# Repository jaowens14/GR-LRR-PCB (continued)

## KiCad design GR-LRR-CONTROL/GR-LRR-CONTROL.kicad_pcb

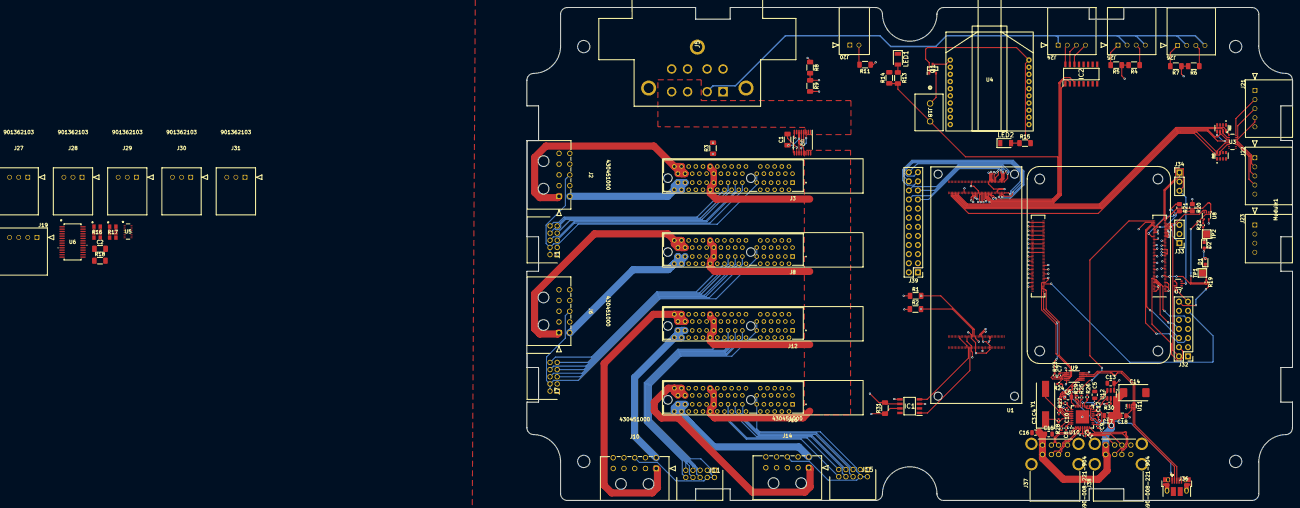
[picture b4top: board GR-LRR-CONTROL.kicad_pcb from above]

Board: 4 copper layers, 213.7 x 137.6 mm, 106 parts (0 on the bottom side), 190 nets.

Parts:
C1: 0.1uF; C_1206_3216Metric_Pad1.33x1.80mm_HandSolder
C2: 10uF; C_1206_3216Metric_Pad1.33x1.80mm_HandSolder
C3, C4: 27pF; C_0402_1005Metric
C5, C6, C13, C15, C16, C17, C18: 10u; C_0805_2012Metric
C7, C8, C9, C10, C11, C12: 100n; C_0402_1005Metric
C14: 100uF; CP_EIA-7343-31_Kemet-D
D1: LED Green; LED_0603_1608Metric
D2: LED Red; LED_0603_1608Metric
IC1: TJA1049T,118
IC2: MC1413DR2G; SOIC127P600X175-16N
J1, J7, J11, J15: 87833-1019
J2, J6, J10, J14: 430451000
J3, J8, J12, J16: 10018783-10101TLF; AMPHENOL_10018783-10101TLF
J5: DT13-08PB; DT1308PB
J18: 691137710002
J19, J23: 901362104
J20: 901362102
J21: ENC1; 901362105
J22: ENC2; 901362105
J24: LED; 901362104
J25: UT1; 901362104
J26: UT2; 901362104
J27, J28, J29, J30, J31: 901362103
J32: Conn_02x07_Odd_Even; PinHeader_2x07_P2.54mm_Vertical
J33, J34: Conn_01x03; PinHeader_1x03_P2.54mm_Vertical
J36: USB_OTG; USB_Micro-B_EDAC_UCON00686
J37, J38: 690-008-221-904; MOLEX_USB_67298-4090
J39: Conn_02x12_Counter_Clockwise; PinHeader_2x12_P2.54mm_Vertical
LED1, LED2: QTLP650C2TR; LEDC3216X130N
Module1: ComputeModule4; Raspberry-Pi-4-Compute-Module
Q1: BSS806NH6327XTSA1; SOT95P240X110-3N
R1, R2, R18: 10k; R_1206_3216Metric_Pad1.30x1.75mm_HandSolder
R3, R31: 120; R_1206_3216Metric_Pad1.30x1.75mm_HandSolder
R4, R6: 4k; R_1206_3216Metric_Pad1.30x1.75mm_HandSolder
R5, R7: 1k 1/8w; R_1206_3216Metric_Pad1.30x1.75mm_HandSolder
R8: 100k 1/8W; R_1206_3216Metric_Pad1.30x1.75mm_HandSolder
R9: 10k 1/8w; R_1206_3216Metric_Pad1.30x1.75mm_HandSolder
R10, R12: YC164-JR-072KL; RESCAXE80P320X160X70-8N
R11, R14: 10k 1/8W; R_1206_3216Metric_Pad1.30x1.75mm_HandSolder
R13, R15: 86ohm, 1/10w; R_1206_3216Metric_Pad1.30x1.75mm_HandSolder
R16, R17: CAY16-221J4LF; CAY16_221J4LF
R19, R22: 1k; R_0402_1005Metric
R20: 0R; R_0805_2012Metric_Pad1.20x1.40mm_HandSolder
R21: nf; R_0805_2012Metric_Pad1.20x1.40mm_HandSolder
R23, R24: 2.2K 1%; R_0402_1005Metric
R25, R26, R27, R29: 36K 1%; R_0402_1005Metric
R28: 12K 1%; R_0402_1005Metric
R30: 15K 1%; R_0402_1005Metric
TP1, TP2: TestPoint; TestPoint_Pad_2.0x2.0mm
U1: ABX00042; MODULE_ABX00042_2
U2: INA260AIPWR; PW0016A_N
U3: 1k; RES_YC248_4X1P6_YAG
U4: XB3-24AST-J
U5: YC248-JR-0710KL; RES_YC248_4X1P6_YAG
U6: PCA9685PW; SOT361-1_NXP
U7, U8: 74LVC1G07SE-7; SOT-353_SC-70-5
U9: FSUSB42MUX; MSOP-10_3x3mm_P0.5mm
U10: USB2514B-I/M2; QFN-36-1EP_6x6mm_P0.5mm_EP3.7x3.7mm
U11: TPD4EUSB30; USON-10_2.5x1.0mm_P0.5mm
U12: AP22653W6; SOT-23-6
Y1: 24MHz; Crystal_SMD_HC49-SD

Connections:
3.3V: C1.2, C5.1, C6.1, C7.1, C8.1, C9.1, C10.1, C11.1, C12.1, D1.2 (A), D2.2 (A), IC1.5 (SPLIT), J5.6, Module1.84 (+3.3v_(Output)), Module1.86 (+3.3v_(Output)), Q1.3 (D), R11.1, R20.1, U2.10 (VS), U4.1 (VCC), U8.5 (VCC), U9.1 (VCC), U10.5 (VDDA33), U10.10 (VDDA33), U10.15 (VDD33), U10.23 (VDD33), U10.27 (VBUS_DET), U10.29 (VDDA33), U10.36 (VDDA33)
5V: C2.1, C13.1, IC1.3 (VCC), J5.7, J19.1, J21.1, J22.1, J23.1, J27.2, J28.2, J29.2, J30.2, J31.2, Module1.77 (+5v_(Input)), Module1.79 (+5v_(Input)), Module1.81 (+5v_(Input)), Module1.83 (+5v_(Input)), Module1.85 (+5v_(Input)), Module1.87 (+5v_(Input)), R1.1, R2.1, U1.J1_21 (VIN), U1.J1_32 (VIN), U1.J1_41 (VIN), U1.J1_48 (VIN), U6.28 (VDD), U7.5 (VCC), U12.1 (IN)
18V: J3.A21, J3.A22, J3.B21, J3.B22, J8.A21, J8.A22, J8.B21, J8.B22, J12.A21, J12.A22, J12.B21, J12.B22, J16.A21, J16.A22, J16.B21, J16.B22, U2.14 (IN-), U2.15 (IN-), U2.16 (IN-)
18V_IN: J5.3, J5.4, U2.1 (IN+), U2.2 (IN+), U2.3 (IN+), U2.12 (VBUS)
24V: J5.2, J24.1, J25.2, J25.4, J26.2, J26.4
/CM4_GPIO ( Ethernet, GPIO, SDCARD)/+1.8v: Module1.88 (+1.8v_(Output)), Module1.90 (+1.8v_(Output)), R21.1
/CM4_GPIO ( Ethernet, GPIO, SDCARD)/AIN0: J32.5, Module1.96 (AnalogIP0)
/CM4_GPIO ( Ethernet, GPIO, SDCARD)/AIN1: J32.6, Module1.94 (AnalogIP1)
/CM4_GPIO ( Ethernet, GPIO, SDCARD)/BT_nDis: J33.3, Module1.91 (BT_nDisable)
/CM4_GPIO ( Ethernet, GPIO, SDCARD)/EEPROM_nWP: J32.4, Module1.20 (EEPROM_nWP)
/CM4_GPIO ( Ethernet, GPIO, SDCARD)/GLOBAL_EN: J32.14, J34.1, Module1.99 (Global_EN)
/CM4_GPIO ( Ethernet, GPIO, SDCARD)/GPIO_VREF: Module1.78 (GPIO_VREF(1.8v/3.3v_Input)), R20.2, R21.2
/CM4_GPIO ( Ethernet, GPIO, SDCARD)/RUN_PG: J34.3, Module1.92 (RUN_PG), U7.2
/CM4_GPIO ( Ethernet, GPIO, SDCARD)/SYNC_IN: J32.8, Module1.16 (Ethernet_SYNC_IN(1.8v))
/CM4_GPIO ( Ethernet, GPIO, SDCARD)/SYNC_OUT: J32.9, Module1.18 (Ethernet_SYNC_OUT(1.8v))
/CM4_GPIO ( Ethernet, GPIO, SDCARD)/TV_OUT: J32.11, Module1.111 (VDAC_COMP)
/CM4_GPIO ( Ethernet, GPIO, SDCARD)/WL_nDis: J33.1, Module1.89 (WL_nDisable)
/CM4_GPIO ( Ethernet, GPIO, SDCARD)/nPWR_LED: Module1.95 (nPI_LED_PWR), U8.2
/CM4_GPIO ( Ethernet, GPIO, SDCARD)/nRPIBOOT: J32.2, Module1.93 (nRPIBOOT)
/CM4_HighSpeed/USB2_N: Module1.103 (USB2_N), U9.4 (D_N)
/CM4_HighSpeed/USB2_P: Module1.105 (USB2_P), U9.3 (D_P)
/CM4_HighSpeed/USBOTG_ID: Module1.101 (USB_OTG_ID), R23.1, R24.2, U9.2 (SEL)
/USB2-HUB/HD1_N: J37.2 (D-`), U10.1 (USBDM_DN1/PRT_DIS_M1)
/USB2-HUB/HD1_P: J37.3 (D+`), U10.2 (USBDP_DN1/PRT_DIS_P1)
/USB2-HUB/HD2_N: J37.6 (D-), U10.3 (USBDM_DN2/PRT_DIS_M2)
/USB2-HUB/HD2_P: J37.7 (D+), U10.4 (USBDP_DN2/PRT_DIS_P2)
/USB2-HUB/HD3_N: J38.2 (D-`), U10.6 (USBDM_DN3/PRT_DIS_M3)
/USB2-HUB/HD3_P: J38.3 (D+`), U10.7 (USBDP_DN3/PRT_DIS_P3)
/USB2-HUB/HD4_N: J38.6 (D-), U10.8 (USBDM_DN4/PRT_DIS_M4)
/USB2-HUB/HD4_P: J38.7 (D+), U10.9 (USBDP_DN4/PRT_DIS_P4)
/USB2-HUB/PWR1: U10.12 (PRTPWR1/BC_EN1), U12.3 (EN)
/USB2-HUB/USBD_N: J36.2 (D-), U9.8 (HSD1_M), U11.4 (D2+), U11.7
/USB2-HUB/USBD_P: J36.3 (D+), U9.9 (HSD1_P), U11.5 (D2-), U11.6
/USB2-HUB/USBH_N: U9.6 (HSD0_M), U10.30 (USBDM_UP)
/USB2-HUB/USBH_P: U9.7 (HSD0_P), U10.31 (USBDP_UP)
/USB2-HUB/VBUS: C14.1, C15.1, C16.1, C17.1, C18.1, J37.1 (VBUS`), J37.5 (VBUS), J38.1 (VBUS`), J38.5 (VBUS), U12.6 (OUT)
/USB2-HUB/nOCS1: U10.13 (OCS_N1), U10.17 (OCS_N2), U10.19 (OCS_N3), U10.21 (OCS_N4), U12.4 (nFault)
/nEXTRST: Module1.100 (nEXTRST), U10.26 (RESET_N)
A3: J39.20, U1.J2_79 (ADC_A3)
A4: J39.21, U1.J2_74 (ADC_A4)
A5: J39.22, U1.J2_76 (ADC_A5)
A6: J39.23, U1.J2_78 (ADC_A6)
A7: J39.24, U1.J2_80 (ADC_A7)
BATT+: J5.5, R8.1
BAT_MON_73_A0: J39.17, R8.2, R9.1, U1.J2_73 (ADC_A0)
CLAMP_C: J20.2, R11.2
D0 ESTOP DETECT: J18.2, J39.10, R13.2, R14.1, U1.J2_62 (PWM_7)
D1: J39.11, U1.J2_60 (PWM_6)
D2: J39.12, U1.J2_67 (PWM_5)
D3: J39.13, U1.J2_65 (PWM_4)
D4: J39.14, U1.J2_63 (PWM_3)
D5 Clamp: J39.15, U1.J2_61 (PWM_2)
D6: J39.16, U1.J2_59 (PWM_1)
D7 CS: J39.9, U1.J2_36 (SPI1_CS)
D8 COPI: J39.6, U1.J2_42 (SPI1_MOSI)
D9 CK: J39.8, U1.J2_38 (SPI1_CK)
D10 CIPO: J39.7, U1.J2_40 (SPI1_MISO)
DVR_+5VOUT_1: J1.2, J1.4, J2.8, J3.A11, J3.B11
DVR_+5VOUT_2: J6.8, J7.2, J7.4, J8.A11, J8.B11
DVR_+5VOUT_3: J10.8, J11.2, J11.4, J12.A11, J12.B11
DVR_+5VOUT_4: J14.8, J15.2, J15.4, J16.A11, J16.B11
DVR_A-/SIN-/LH1_1: J1.5, J3.A13
DVR_A-/SIN-/LH1_2: J7.5, J8.A13
DVR_A-/SIN-/LH1_3: J11.5, J12.A13
DVR_A-/SIN-/LH1_4: J15.5, J16.A13
DVR_A/A+_1: J2.1, J3.B29, J3.B30, J3.B31, J3.B32
DVR_A/A+_2: J6.1, J8.B29, J8.B30, J8.B31, J8.B32
DVR_A/A+_3: J10.1, J12.B29, J12.B30, J12.B31, J12.B32
DVR_A/A+_4: J14.1, J16.B29, J16.B30, J16.B31, J16.B32
DVR_A/SIN+_1: J1.6, J3.A14
DVR_A/SIN+_2: J7.6, J8.A14
DVR_A/SIN+_3: J11.6, J12.A14
DVR_A/SIN+_4: J15.6, J16.A14
DVR_B-/COS-/LH2_1: J1.7, J3.A15
DVR_B-/COS-/LH2_2: J7.7, J8.A15
DVR_B-/COS-/LH2_3: J11.7, J12.A15
DVR_B-/COS-/LH2_4: J15.7, J16.A15
DVR_BR/B-_1: J2.7, J3.A25, J3.A26, J3.A27, J3.A28
DVR_BR/B-_2: J6.7, J8.A25, J8.A26, J8.A27, J8.A28
DVR_BR/B-_3: J10.7, J12.A25, J12.A26, J12.A27, J12.A28
DVR_BR/B-_4: J14.7, J16.A25, J16.A26, J16.A27, J16.A28
DVR_B/A-_1: J2.6, J3.A29, J3.A30, J3.A31, J3.A32
DVR_B/A-_2: J6.6, J8.A29, J8.A30, J8.A31, J8.A32
DVR_B/A-_3: J10.6, J12.A29, J12.A30, J12.A31, J12.A32
DVR_B/A-_4: J14.6, J16.A29, J16.A30, J16.A31, J16.A32
DVR_B/COS+_1: J1.8, J3.A16
DVR_B/COS+_2: J7.8, J8.A16
DVR_B/COS+_3: J11.8, J12.A16
DVR_B/COS+_4: J15.8, J16.A16
DVR_CAN_1_+: IC1.7 (CANH), J3.A19, J8.A19, J12.A19, J16.A19, R3.1, R31.1
DVR_CAN_1_-: IC1.6 (CANL), J3.B19, J8.B19, J12.B19, J16.B19, R3.2, R31.2
DVR_C/B+_1: J2.2, J3.B25, J3.B26, J3.B27, J3.B28
DVR_C/B+_2: J6.2, J8.B25, J8.B26, J8.B27, J8.B28
DVR_C/B+_3: J10.2, J12.B25, J12.B26, J12.B27, J12.B28
DVR_C/B+_4: J14.2, J16.B25, J16.B26, J16.B27, J16.B28
DVR_HALL1_1: J2.3, J3.A8
DVR_HALL1_2: J6.3, J8.A8
DVR_HALL1_3: J10.3, J12.A8
DVR_HALL1_4: J14.3, J16.A8
DVR_HALL2_1: J2.4, J3.A9
DVR_HALL2_2: J6.4, J8.A9
DVR_HALL2_3: J10.4, J12.A9
DVR_HALL2_4: J14.4, J16.A9
DVR_HALL3_1: J2.5, J3.A10
DVR_HALL3_2: J6.5, J8.A10
DVR_HALL3_3: J10.5, J12.A10
DVR_HALL3_4: J14.5, J16.A10
DVR_Z+_1: J1.10, J3.A18
DVR_Z+_2: J7.10, J8.A18
DVR_Z+_3: J11.10, J12.A18
DVR_Z+_4: J15.10, J16.A18
DVR_Z-/LH3_1: J1.9, J3.A17
DVR_Z-/LH3_2: J7.9, J8.A17
DVR_Z-/LH3_3: J11.9, J12.A17
DVR_Z-/LH3_4: J15.9, J16.A17
ENCODER1_PHASEA: R12.8, U1.J2_16 (CAM_D0), U3.1
ENCODER1_PHASEA_IN: J21.2, U3.16
ENCODER1_PHASEB: R12.7, U1.J2_14 (CAM_D1), U3.2
ENCODER1_PHASEB_IN: J21.3, U3.15
ENCODER1_PHASEZ: R12.6, U1.J2_12 (CAM_D2), U3.3
ENCODER1_PHASEZ_IN: J21.4, U3.14
ENCODER2_PHASEA: R12.5, U1.J2_10 (CAM_D3), U3.4
ENCODER2_PHASEA_IN: J22.2, U3.13
ENCODER2_PHASEB: R10.8, U1.J2_8 (CAM_D4), U3.5
ENCODER2_PHASEB_IN: J22.3, U3.12
ENCODER2_PHASEZ: R10.7, U1.J2_6 (CAM_D5), U3.6
ENCODER2_PHASEZ_IN: J22.4, U3.11
GND: C1.1, C2.2, C3.2, C4.2, C5.2, C6.2, C7.2, C8.2, C9.2, C10.2, C11.2, C12.2, C13.2, C14.2, C15.2, C16.2, C17.2, C18.2, IC1.2 (GND), IC2.8 (GND), J1.1, J1.3, J2.9, J2.10, J3.A1, J3.A12, J3.A20, J3.A23, J3.A24, J3.B1, J3.B5, J3.B23, J3.B24, J5.1, J5.8, J6.9, J6.10, J7.1, J7.3, J8.A1, J8.A12, J8.A20, J8.A23, J8.A24, J8.B1, J8.B5, J8.B23, J8.B24, J10.9, J10.10, J11.1, J11.3, J12.A1, J12.A12, J12.A20, J12.A23, J12.A24, J12.B1, J12.B5, J12.B23, J12.B24, J14.9, J14.10, J15.1, J15.3, J16.A1, J16.A12, J16.A20, J16.A23, J16.A24, J16.B1, J16.B5, J16.B23, J16.B24, J19.4, J21.5, J22.5, J23.4, J25.1, J26.1, J27.3, J28.3, J29.3, J30.3, J31.3, J32.1, J32.3, J32.7, J32.10, J32.12, J33.2, J34.2, J36.5 (GND), J36.6 (Shield), J37.4 (GND`), J37.8 (GND), J37.MT1, J37.MT2, J37.MT3, J37.MT4, J38.4 (GND`), J38.8 (GND), J38.MT1, J38.MT2, J38.MT3, J38.MT4, LED1.1 (K), LED2.1 (K), Module1.1 (GND), Module1.2 (GND), Module1.7 (GND), Module1.8 (GND), Module1.13 (GND), Module1.14 (GND), Module1.22 (GND), Module1.23 (GND), Module1.32 (GND), Module1.33 (GND), Module1.42 (GND), Module1.43 (GND), Module1.52 (GND), Module1.53 (GND), Module1.59 (GND), Module1.60 (GND), Module1.65 (GND), Module1.66 (GND), Module1.71 (GND), Module1.74 (GND), Module1.98 (GND), Module1.107 (GND), Module1.108 (GND), Module1.113 (GND), Module1.114 (GND), Module1.119 (GND), Module1.120 (GND), Module1.125 (GND), Module1.126 (GND), Module1.131 (GND), Module1.132 (GND), Module1.137 (GND), Module1.138 (GND), Module1.144 (GND), Module1.150 (GND), Module1.155 (GND), Module1.156 (GND), Module1.161 (GND), Module1.162 (GND), Module1.167 (GND), Module1.168 (GND), Module1.173 (GND), Module1.174 (GND), Module1.179 (GND), Module1.180 (GND), Module1.185 (GND), Module1.186 (GND), Module1.191 (GND), Module1.192 (GND), Module1.197 (GND), Module1.198 (GND), R5.2, R7.2, R9.2, R10.1, R10.2, R10.3, R10.4, R12.1, R12.2, R12.3, R12.4, R14.2, R18.2, R23.2, R25.2, R26.2, R27.2, R28.1, R29.2, R30.2, U1.J1_22 (GND), U1.J1_42 (GND), U1.J2_24 (GND_1), U1.J2_33 (GND_1), U1.J2_44 (GND_1), U1.J2_57 (GND_1), U1.J2_70 (GND_1), U2.6 (GND), U2.11 (GND), U2.13 (NC), U4.10 (GND), U5.3, U5.4, U5.5, U5.6, U5.7, U5.8, U6.14 (VSS), U6.25 (EXTCLK), U7.3 (GND), U8.3 (GND), U9.5 (GND), U9.10 (nOE), U10.37 (VSS), U11.3 (GND), U11.8 (GND), U12.2 (GND)
GPIO0: J39.5, U1.J2_46 (GPIO_0)
GPIO1: J39.4, U1.J2_48 (GPIO_1)
GPIO2: J39.3, U1.J2_50 (GPIO_2)
GPIO3: J39.2, U1.J2_52 (GPIO_3)
GPIO4 RED LED: IC2.1 (IN_1), J39.1, U1.J2_54 (GPIO_4)
GPIO5 YELLOW LED: IC2.2 (IN_2), U1.J2_56 (GPIO_5)
GPIO6 GREEN LED: IC2.3 (IN_3), U1.J2_58 (GPIO_6)
H7_CAN1_RX: IC1.4 (RXD), U1.J1_51 (CAN1_RX)
H7_CAN1_TX: IC1.1 (TXD), U1.J1_49 (CAN1_TX)
H7_I2C0_SCL: J19.3, J23.3, R2.2, U1.J1_46 (I2C0_SCL), U2.4 (A1), U2.5 (A0), U2.9 (SCL), U6.26 (SCL)
H7_I2C0_SDA: J19.2, J23.2, R1.2, U1.J1_44 (I2C0_SDA), U2.8 (SDA), U6.27 (SDA)
LED_GREEN: IC2.14 (OUT_5), J24.4
LED_RED: IC2.16 (OUT_7), J24.2
LED_YELLOW: IC2.15 (OUT_6), J24.3
unnamed: D1.1 (K), R19.1, TP1.1
unnamed: D2.1 (K), R22.1, TP2.1
unnamed: J32.13, U7.4
unnamed: J36.1 (VBUS), R24.1
unnamed: LED1.2 (A), R13.1
unnamed: LED2.2 (A), R15.1
unnamed: Module1.21 (PI_nLED_Activity), R19.2
unnamed: J18.1, Q1.2 (S)
unnamed: R22.2, U8.4
unnamed: U1.J1_31 (GND), U1.J1_47 (GND), U1.J1_54 (GND)
unnamed: U1.J1_53 (VSYS), U1.J1_64 (VSYS)
unnamed: R18.1, U6.23 (*OE)
unnamed: U5.14, U6.1 (A0)
unnamed: U5.13, U6.2 (A1)
unnamed: U5.12, U6.3 (A2)
unnamed: U5.11, U6.4 (A3)
unnamed: U5.10, U6.5 (A4)
unnamed: U5.9, U6.24 (A5)
unnamed: R16.8, U6.6 (LED0)
unnamed: R16.7, U6.7 (LED1)
unnamed: R16.6, U6.8 (LED2)
unnamed: R16.5, U6.9 (LED3)
unnamed: R17.8, U6.10 (LED4)
unnamed: R17.7, U6.11 (LED5)
unnamed: R17.6, U6.12 (LED6)
unnamed: R17.5, U6.13 (LED7)
unnamed: R29.1, U10.25 (HS_IND/CFG_SEL1)
unnamed: R28.2, U10.35 (RBIAS)
unnamed: R25.1, U10.24 (SCL/SMBCLK/CFG_SEL0)
unnamed: R26.1, U10.22 (SDA/SMBDATA/NON_REM1)
unnamed: R27.1, U10.28 (SUSP_IND/LOCAL_PWR/NON_REM0)
unnamed: C3.1, U10.33 (XTALIN/CLKIN), Y1.1
unnamed: C4.1, U10.32 (XTALOUT), Y1.2
unnamed: U11.1 (D1+), U11.10
unnamed: U11.2 (D1-), U11.9
unnamed: R30.1, U12.5 (ILIM)
PWM0: J27.1, R16.1
PWM1: J28.1, R16.2
PWM2: J29.1, R16.3
PWM3: J30.1, R16.4
PWM4: J31.1, R17.1
RPI_GPIO_14_TX: Module1.55 (GPIO14), U1.J1_36 (UART0_RX)
RPI_GPIO_15_RX: Module1.51 (GPIO15), U1.J1_34 (UART0_TX)
UT1_75_A1: J39.18, R4.2, R5.1, U1.J2_75 (ADC_A1)
UT1_SIGNAL: J25.3, R4.1
UT2_77_A2: J39.19, R6.2, R7.1, U1.J2_77 (ADC_A2)
UT2_SIGNAL: J26.3, R6.1
ZIGBEE_IO: Q1.1 (G), R15.2, U4.20 (AD0/DIO0)

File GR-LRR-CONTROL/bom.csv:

In Cart,Reference,Value,Part Number,Datasheet,Footprint,Qty,DNP
yes,"C3,C4",27pF,GJM1555C1H270JB01D,https://search.murata.co.jp/Ceramy/image/img/A01X/G101/ENG/G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,Capacitor_SMD:C_0402_1005Metric,2,
yes,"C5,C6,C13,C15,C16,C17,C18",10u,GRM21BR71A106KA73L,https://search.murata.co.jp/Ceramy/image/img/A01X/G101/ENG/G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,Capacitor_SMD:C_0805_2012Metric,7,
yes,"C7,C8,C9,C10,C11,C12",100n,RM EMK105 B7104KV-F,https://search.murata.co.jp/Ceramy/image/img/A01X/G101/ENG/G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,Capacitor_SMD:C_0402_1005Metric,6,
yes,C14,100uF,EEF-CX0J101R,~,Capacitor_Tantalum_SMD:CP_EIA-7343-31_Kemet-D,1,
yes,"C19,C20,C21,C22",ECA-2AHG471,ECA-2AHG471,ECA-2AHG471,avid_footprints:ECA_2AHG471,4,
yes,"CR1,CR2",PMEG6020ER_115,PMEG6020ER_115,PMEG6020ER_115,avid_footprints:CFP3_SOD123W_NEX,2,
yes,D1,LED Green,LTST-S270KGKT,http://optoelectronics.liteon.com/upload/download/DS22-2000-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,LED_SMD:LED_0603_1608Metric,1,
yes,D2,LED Red,LTST-S270KRKT,http://optoelectronics.liteon.com/upload/download/DS22-2000-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,LED_SMD:LED_0603_1608Metric,1,
yes,IC1,"TJA1049T,118","TJA1049T,118",http://www.nxp.com/docs/en/data-sheet/TJA1049.pdf,"avid_footprints:TJA1049T,118",1,
yes,IC2,MC1413DR2G,MC1413DR2G,https://www.3dcontentcentral.cn/download-model.aspx?catalogi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,avid_footprints:SOIC127P600X175-16N,1,
yes,"J1,J7,J11,J15",87833-1019,87833-1019,https://www.molex.com/pdm_docs/sd/878331019_sd.pdf,avid_footprints:87833-1019,4,
yes,"J2,J6,J10,J14",430451000,430451000,430451000,avid_footprints:430451000,4,
yes,"J3,J8,J12,J16",10018783-10101TLF,10018783-10101TLF,,avid_footprints:AMPHENOL_10018783-10101TLF,4,
,"J4,J39",Conn_02x12_Counter_Clockwise,,~,Connector_PinHeader_2.54mm:PinHeader_2x12_P2.54mm_Vertical,2,
Mouser,J5,DT13-08PB,DT13-08PB,https://www.te.com/commerce/DocumentDelivery/DDEController?A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,avid_footprints:DT1308PB,1,
Yes,J18,691137710002,691137710002,691137710002,avid_footprints:691137710002,1,
yes,J20,901362102,901362102,901362102,avid_footprints:901362102,1,
yes,J21,ENC1,901362105,901362105,avid_footprints:901362105,1,
yes,J22,ENC2,901362105,901362105,avid_footprints:901362105,1,
yes,J23,901362104,901362104,901362104,avid_footprints:901362104,1,
yes,"J24,J25,J26",LED,901362104,901362104,avid_footprints:901362104,3,
,J32,Conn_02x07_Odd_Even,DNP,https://www.toby.co.uk/uploads/publications/1673.pdf,Connector_PinHeader_2.54mm:PinHeader_2x07_P2.54mm_Vertical,1,
,"J33,J34",Conn_01x03,DNP,~,Connector_PinHeader_2.54mm:PinHeader_1x03_P2.54mm_Vertical,2,
yes,J36,USB_OTG,10103594-0001LF,https://cdn.amphenol-icc.com/media/wysiwyg/files/documentati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,avid_footprints:USB_Micro-B_EDAC_UCON00686,1,
yes,"J37,J38",690-008-221-904,672984090,https://www.molex.com/pdm_docs/sd/672984090_sd.pdf,avid_footprints:MOLEX_USB_67298-4090,2,
Yes,"LED1,LED2",QTLP650C2TR,QTLP650C2TR,"https://media.digikey.com/pdf/Data%20Sheets/Everlight%20PDFs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,D)-2,3,4,7,B.pdf",avid_footprints:LEDC3216X130N,2,
yes,Module1,ComputeModule4,,,avid_footprints:Raspberry-Pi-4-Compute-Module,1,
yes,Q1,BSS806NH6327XTSA1,BSS806NH6327XTSA1,https://www.infineon.com/dgdl/Infineon-BSS806N-DS-v02_03-en.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,SOT95P240X110-3N,1,
yes,"R1,R2,R9,R11,R14",10k,RNCS1206BKE10K0,~,Resistor_SMD:R_1206_3216Metric_Pad1.30x1.75mm_HandSolder,5,
Yes,"R3,R31",120 1/4W,RT1206DRE07120RL,~,Resistor_SMD:R_1206_3216Metric_Pad1.30x1.75mm_HandSolder,2,
yes,"R4,R6",4k,RMCF1206FT4K02,~,Resistor_SMD:R_1206_3216Metric_Pad1.30x1.75mm_HandSolder,2,
yes,"R5,R7",1k 1/8w,RNCS1206BKE1K00,~,Resistor_SMD:R_1206_3216Metric_Pad1.30x1.75mm_HandSolder,2,
yes,R8,100k 1/8W,RNCS1206BKE100K,~,Resistor_SMD:R_1206_3216Metric_Pad1.30x1.75mm_HandSolder,1,
yes,"R10,R12",YC164-JR-072KL,YC164-JR-072KL,,avid_footprints:RESCAXE80P320X160X70-8N,2,
yes,"R13,R15","86ohm, 1/10w",RC1206FR-0786R6L,~,Resistor_SMD:R_1206_3216Metric_Pad1.30x1.75mm_HandSolder,2,
yes,"R16,R33",22k,RC1206FR-0722KL,~,Resistor_SMD:R_1206_3216Metric_Pad1.30x1.75mm_HandSolder,2,
yes,"R19,R22",1k,RK73H1ETTP1001F,https://fscdn.rohm.com/en/products/databook/datasheet/passiv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,Resistor_SMD:R_0402_1005Metric,2,
,R20,0R,,https://fscdn.rohm.com/en/products/databook/datasheet/passiv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,Resistor_SMD:R_0805_2012Metric_Pad1.20x1.40mm_HandSolder,1,
,R21,nf,,https://fscdn.rohm.com/en/products/databook/datasheet/passiv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,Resistor_SMD:R_0805_2012Metric_Pad1.20x1.40mm_HandSolder,1,
yes,"R23,R24",2.2K 1%,RC0402FR-072K2L,https://fscdn.rohm.com/en/products/databook/datasheet/passiv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,Resistor_SMD:R_0402_1005Metric,2,
yes,"R25,R26,R27,R29",36K 1%,CRCW040236K0FKED,https://fscdn.rohm.com/en/products/databook/datasheet/passiv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,Resistor_SMD:R_0402_1005Metric,4,
,R28,12K 1%,RC0402FR-0712KL ,https://fscdn.rohm.com/en/products/databook/datasheet/passiv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,Resistor_SMD:R_0402_1005Metric,1,
yes,R30,15K 1%,CRCW040215K0FKED,https://fscdn.rohm.com/en/products/databook/datasheet/passiv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,Resistor_SMD:R_0402_1005Metric,1,
Yes,R32,4.7k,RC1206JR-074K7L,~,Resistor_SMD:R_1206_3216Metric_Pad1.30x1.75mm_HandSolder,1,
yes,SW1,XA1E-BV302-R,XA1E-BV302-R,,XA1E-BV302-R:XA1E-BV302-R,1,
,"TP1,TP2",TestPoint,,,TestPoint:TestPoint_Pad_2.0x2.0mm,2,
"Yes, connectors",U1,ABX00042,Portenta H7,,avid_footprints:MODULE_ABX00042_2,1,
yes,U3,1k,YC248-JR-071KL ,YC248-JR-071KL ,avid_footprints:RES_YC248_4X1P6_YAG,1,
yes,U4,~,XB3-24AST-J,,avid_footprints:XB3-24AST-J,1,
yes,"U7,U8",74LVC1G07SE-7,74LVC1G07SE-7,https://www.diodes.com/assets/Datasheets/74LVC1G07.pdf,Package_TO_SOT_SMD:SOT-353_SC-70-5,2,
yes,U9,FSUSB42MUX,FSUSB42MUX,https://www.onsemi.com/pub/Collateral/FSUSB42-D.PDF,Package_SO:MSOP-10_3x3mm_P0.5mm,1,
yes,U10,USB2514B-I/M2,USB2514B-I/M2,http://ww1.microchip.com/downloads/en/DeviceDoc/00001692C.pdf,Package_DFN_QFN:QFN-36-1EP_6x6mm_P0.5mm_EP3.7x3.7mm,1,
yes,U11,TPD4EUSB30,CDDFN10-3324P,http://www.ti.com/lit/ds/symlink/tpd2eusb30a.pdf,Package_SON:USON-10_2.5x1.0mm_P0.5mm,1,
yes,U12,AP22653W6,AP22653W6,https://www.diodes.com/assets/Datasheets/AP255x.pdf,Package_TO_SOT_SMD:SOT-23-6,1,
Newark,Y1,24MHz,QCS24.0000F18B23M,~,Crystal:Crystal_SMD_HC49-SD,1,

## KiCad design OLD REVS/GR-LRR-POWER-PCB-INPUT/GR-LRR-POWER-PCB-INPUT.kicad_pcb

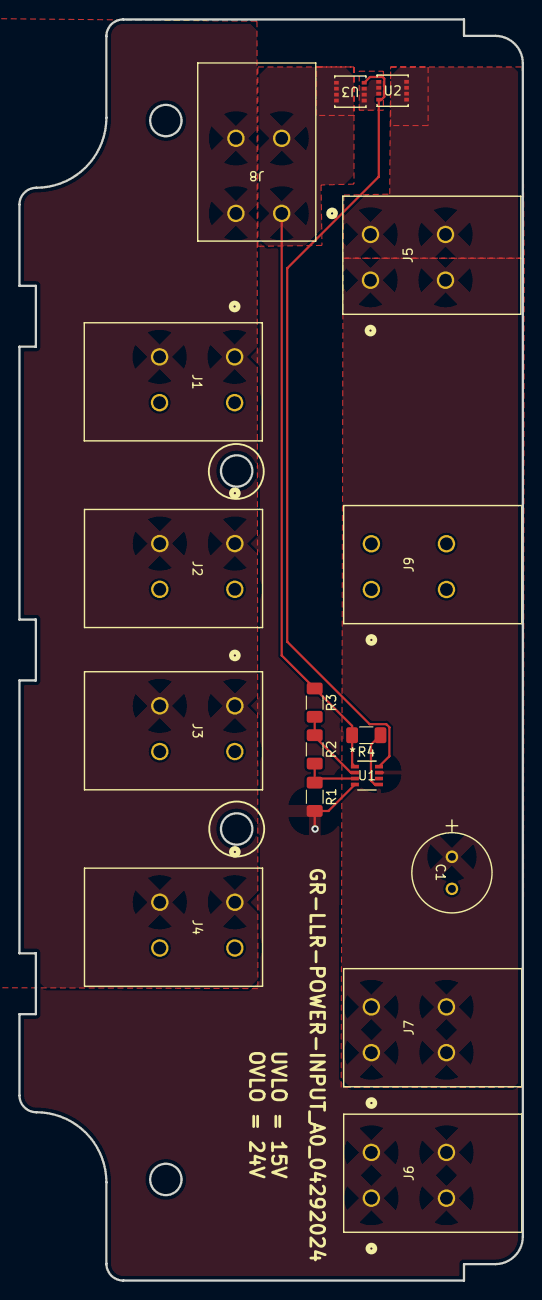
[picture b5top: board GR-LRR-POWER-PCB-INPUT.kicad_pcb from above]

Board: 2 copper layers, 55.0 x 137.8 mm, 17 parts (0 on the bottom side), 9 nets.

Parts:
C1: 50ZLH100MEFC8X11.5; CAP_YX_8X11P5_RUB
J1: BATT1; 2604
J2: BATT2; 2604
J3: BATT3; 2604
J4: BATT4; 2604
J5, J7: BATT+; 2604
J6, J9: -BUS; 2604
J8: SWITCH; 2604
R1: 187k; R_1206_3216Metric_Pad1.30x1.75mm_HandSolder
R2: 113k; R_1206_3216Metric_Pad1.30x1.75mm_HandSolder
R3: 8700k; R_1206_3216Metric_Pad1.30x1.75mm_HandSolder
R4: 100k; R_1206_3216Metric_Pad1.30x1.75mm_HandSolder
U1: LTC4365CTS8-TRMPBF; TSOT-23_TS8_LIT
U2, U3: SIS434DN-T1-GE3; MOSFET_4DN-T1-E3_VIS

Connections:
BG: C1.2, J1.2_1, J1.2_2, J2.2_1, J2.2_2, J3.2_1, J3.2_2, J4.2_1, J4.2_2, J6.1_1, J6.1_2, J6.2_1, J6.2_2, J9.1_1, J9.1_2, J9.2_1, J9.2_2, R1.2, U1.4 (GND)
BV: J8.1_1, J8.1_2, R3.1, R4.2, U1.1 (VIN), U3.5 (D), U3.6 (D), U3.7 (D), U3.8 (D)
BV1: J1.1_1, J1.1_2, J2.1_1, J2.1_2, J3.1_1, J3.1_2, J4.1_1, J4.1_2, J8.2_1, J8.2_2
BV_OUT: C1.1, J5.1_1, J5.1_2, J5.2_1, J5.2_2, J7.1_1, J7.1_2, J7.2_1, J7.2_2, U1.7 (VOUT), U2.5 (D), U2.6 (D), U2.7 (D), U2.8 (D)
unnamed: R4.1, U1.5 (*SHDN)
unnamed: U1.8 (GATE), U2.4 (G), U3.4 (G)
unnamed: R1.1, R2.2, U1.3 (OV)
unnamed: R2.1, R3.2, U1.2 (UV)
unnamed: U2.1 (S), U2.2 (S), U2.3 (S), U3.1 (S), U3.2 (S), U3.3 (S)

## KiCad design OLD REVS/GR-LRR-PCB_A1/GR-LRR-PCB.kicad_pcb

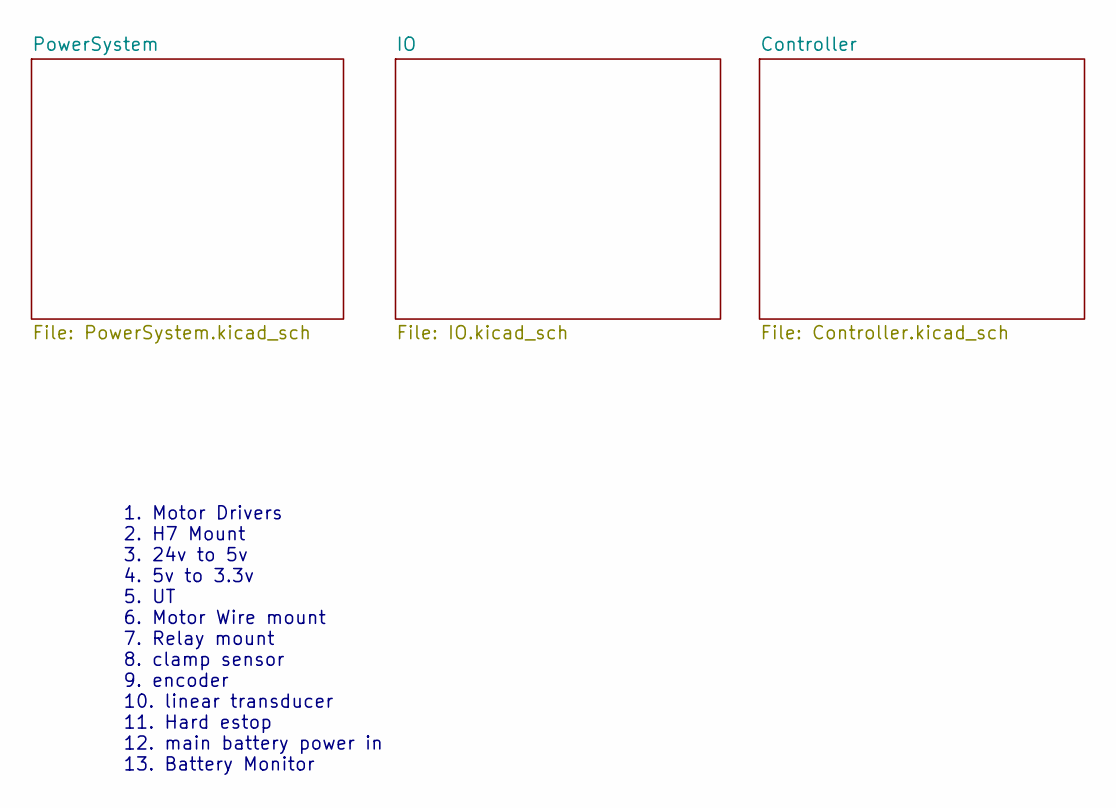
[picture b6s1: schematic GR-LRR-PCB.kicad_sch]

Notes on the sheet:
1. Motor Drivers 2. H7 Mount 3. 24v to 5v 4. 5v to 3.3v 5. UT 6. Motor Wire mount 7. Relay mount 8. clamp sensor 9. encoder 10. linear transducer 11. Hard estop 12. main battery power in 13. Battery Monitor

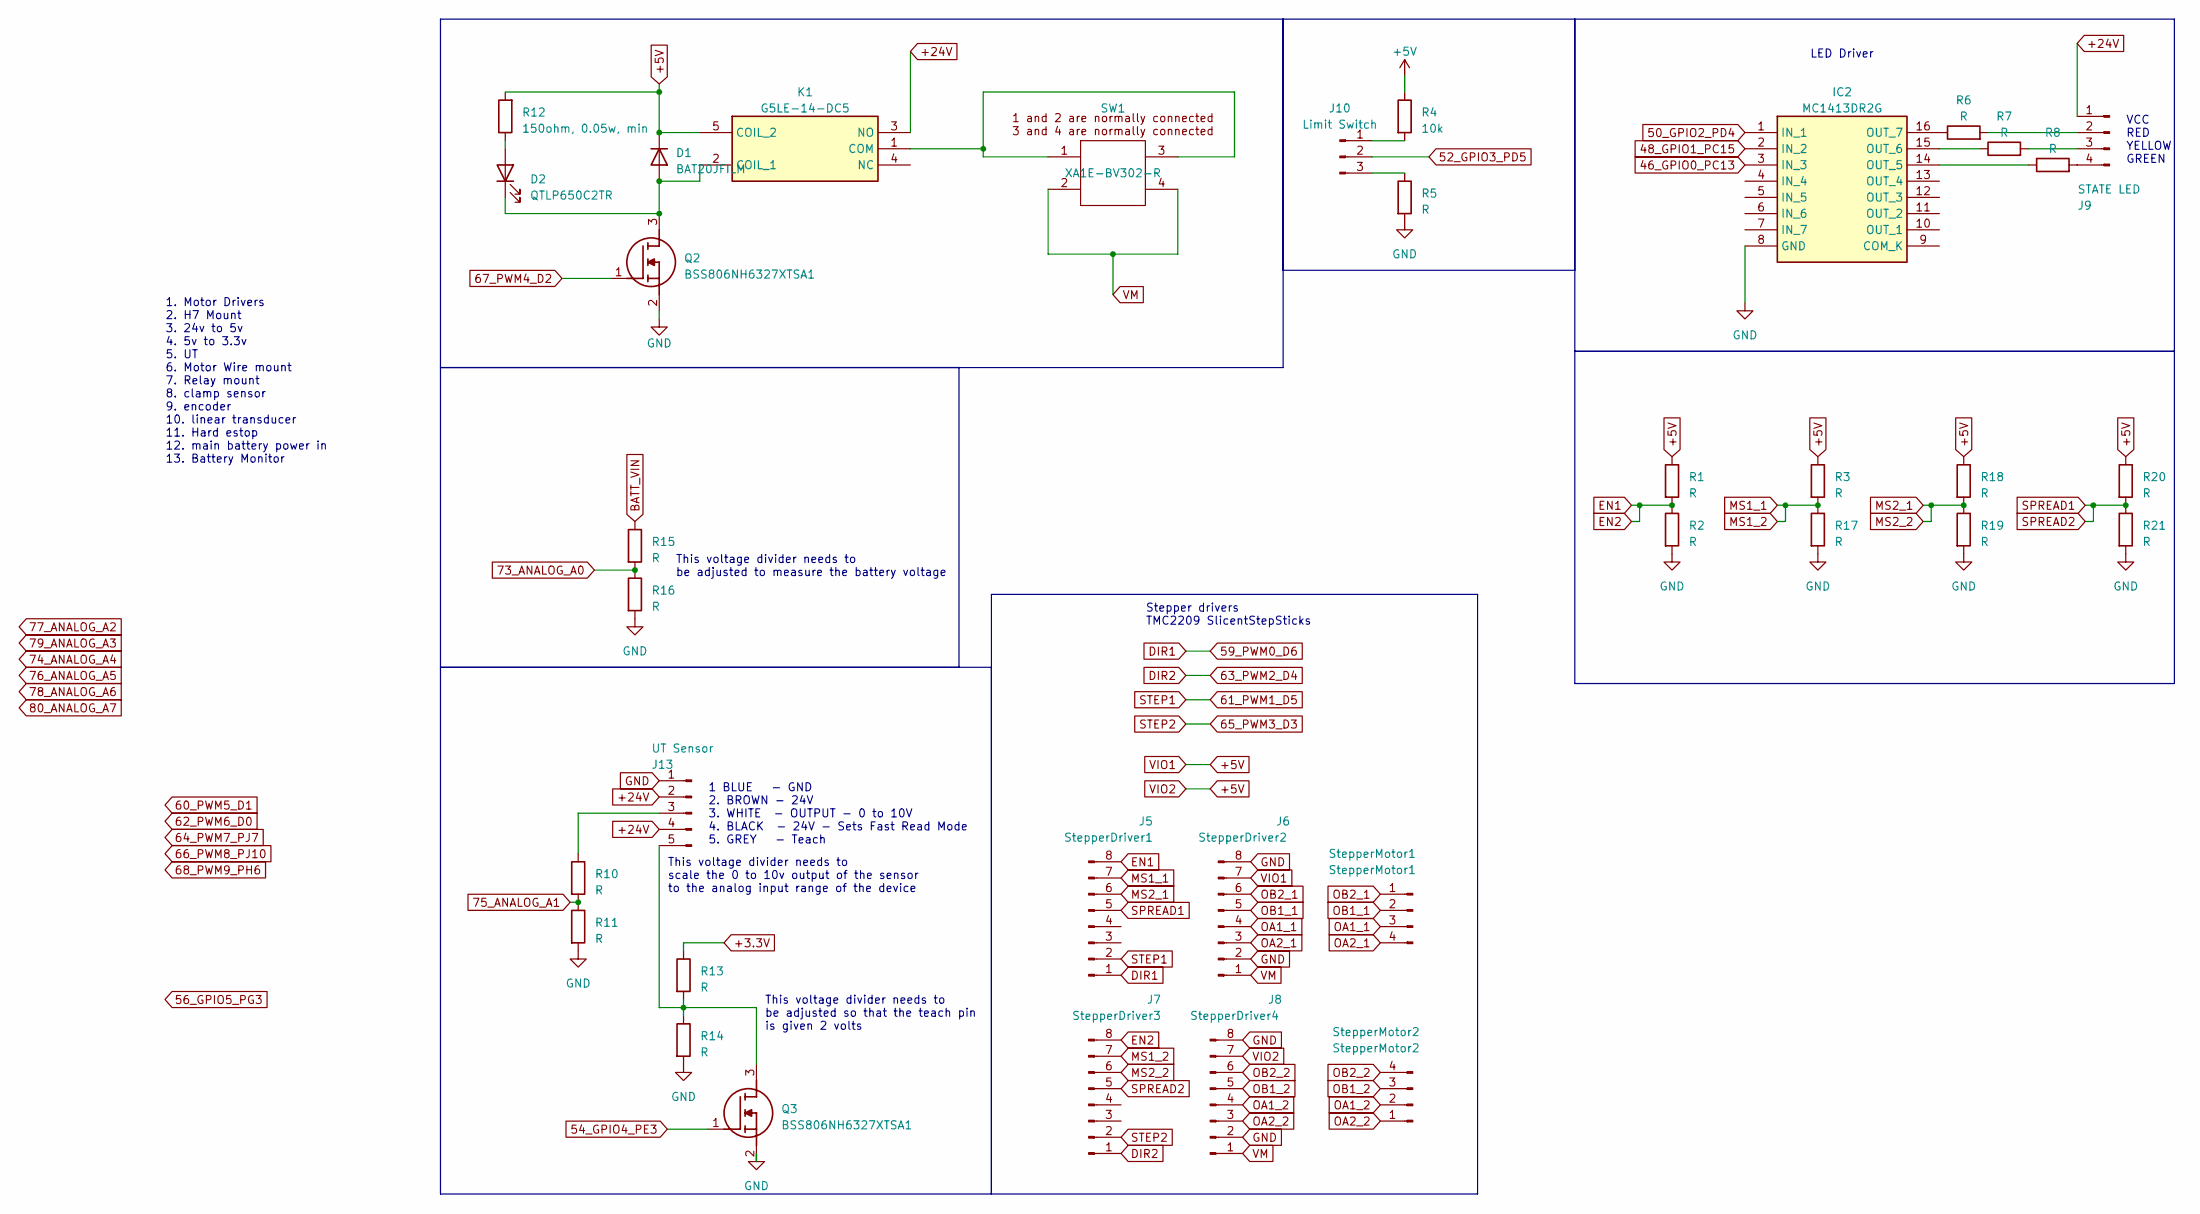
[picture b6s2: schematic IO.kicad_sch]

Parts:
D1: BAT20JFILM; D_SOD-323_HandSoldering
D2: QTLP650C2TR; D_1206_3216Metric_Pad1.42x1.75mm_HandSolder
IC2: MC1413DR2G; SOIC127P600X175-16N; Mouser Part Number 863-MC1413DR2G
J5: StepperDriver1; PinHeader_1x08_P2.54mm_Vertical
J6: StepperDriver2; PinHeader_1x08_P2.54mm_Vertical
J7: StepperDriver3; PinHeader_1x08_P2.54mm_Vertical
J8: StepperDriver4; PinHeader_1x08_P2.54mm_Vertical
J9: STATE LED; PinHeader_1x04_P2.54mm_Vertical; Part Number JR28-RYG-D
J10: Limit Switch; PinHeader_1x03_P2.54mm_Vertical
J13: UT Sensor; PinHeader_1x05_P2.54mm_Vertical
K1: G5LE-14-DC5; G5LE-14_SPDT; Mouser Part Number 653-G5LE-14-DC5
Q2, Q3: BSS806NH6327XTSA1; SOT95P240X110-3N; Mouser Part Number 726-BSS806NH6327
R1, R2, R3, R5, R6, R7, R8, R10, R11, R13, R14, R15, R16, R17, R18, R19, R20, R21: R; R_1206_3216Metric_Pad1.30x1.75mm_HandSolder
R4: 10k; R_1206_3216Metric_Pad1.30x1.75mm_HandSolder
R12: 150ohm, 0.05w, min; R_1206_3216Metric_Pad1.30x1.75mm_HandSolder; Part Number RMCF1206JT300R
SW1: XA1E-BV302-R
StepperMotor1: StepperMotor1; PinHeader_1x04_P2.54mm_Vertical
StepperMotor2: StepperMotor2; PinHeader_1x04_P2.54mm_Vertical

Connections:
46_GPIO0_PC13: IC2.3 (IN_3); also elsewhere on the board
48_GPIO1_PC15: IC2.2 (IN_2); also elsewhere on the board
50_GPIO2_PD4: IC2.1 (IN_1); also elsewhere on the board
52_GPIO3_PD5: J10.2; also elsewhere on the board
54_GPIO4_PE3: Q3.1 (G); also elsewhere on the board
59_PWM0_D6: J5.1; also elsewhere on the board
61_PWM1_D5: J5.2; also elsewhere on the board
63_PWM2_D4: J7.1; also elsewhere on the board
65_PWM3_D3: J7.2; also elsewhere on the board
67_PWM4_D2: Q2.1 (G); also elsewhere on the board
73_ANALOG_A0: R15.2, R16.1; also elsewhere on the board
75_ANALOG_A1: R10.2, R11.1; also elsewhere on the board
+3.3V: R13.1; also elsewhere on the board
+5V: D1.1 (K), J6.7, J8.7, K1.5 (COIL_2), R1.1, R3.1, R4.1, R12.2, R18.1, R20.1; also elsewhere on the board
+24V: J9.1, J13.2, J13.4, K1.3 (NO); also elsewhere on the board
BATT_VIN: R15.1; also elsewhere on the board
EN1: J5.8, J7.8, R1.2, R2.1
GND: IC2.8 (GND), J6.2, J6.8, J8.2, J8.8, J13.1, Q2.2 (S), Q3.2 (S), R2.2, R5.2, R11.2, R14.2, R16.2, R17.2, R19.2, R21.2; also elsewhere on the board
MS1_1: J5.7, J7.7, R3.2, R17.1
MS2_1: J5.6, J7.6, R18.2, R19.1
unnamed: D1.2 (A), D2.1 (K), K1.2 (COIL_1), Q2.3 (D)
unnamed: D2.2 (A), R12.1
unnamed: IC2.14 (OUT_5), R8.1
unnamed: IC2.15 (OUT_6), R7.1
unnamed: IC2.16 (OUT_7), R6.1
unnamed: J9.2, R6.2
unnamed: J9.3, R7.2
unnamed: J9.4, R8.2
unnamed: J10.1, R4.2
unnamed: J10.3, R5.1
unnamed: J13.3, R10.1
unnamed: J13.5, Q3.3 (D), R13.2, R14.1
unnamed: K1.1 (COM), SW1.1, SW1.3
OA1_1: J6.4, StepperMotor1.3
OA1_2: J8.4, StepperMotor2.2
OA2_1: J6.3, StepperMotor1.4
OA2_2: J8.3, StepperMotor2.1
OB1_1: J6.5, StepperMotor1.2
OB1_2: J8.5, StepperMotor2.3
OB2_1: J6.6, StepperMotor1.1
OB2_2: J8.6, StepperMotor2.4
SPREAD1: J5.5, J7.5, R20.2, R21.1
VM: J6.1, J8.1, SW1.2, SW1.4

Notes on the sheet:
This voltage divider needs to be adjusted to measure the battery voltage
LED Driver
VCC RED YELLOW GREEN
1. Motor Drivers 2. H7 Mount 3. 24v to 5v 4. 5v to 3.3v 5. UT 6. Motor Wire mount 7. Relay mount 8. clamp sensor 9. encoder 10. linear transducer 11. Hard estop 12. main battery power in 13. Battery Monitor
1 BLUE - GND 2. BROWN - 24V 3. WHITE - OUTPUT - 0 to 10V 4. BLACK - 24V - Sets Fast Read Mode 5. GREY - Teach
This voltage divider needs to be adjusted so that the teach pin is given 2 volts
Stepper drivers TMC2209 SlicentStepSticks
This voltage divider needs to scale the 0 to 10v output of the sensor to the analog input range of the device

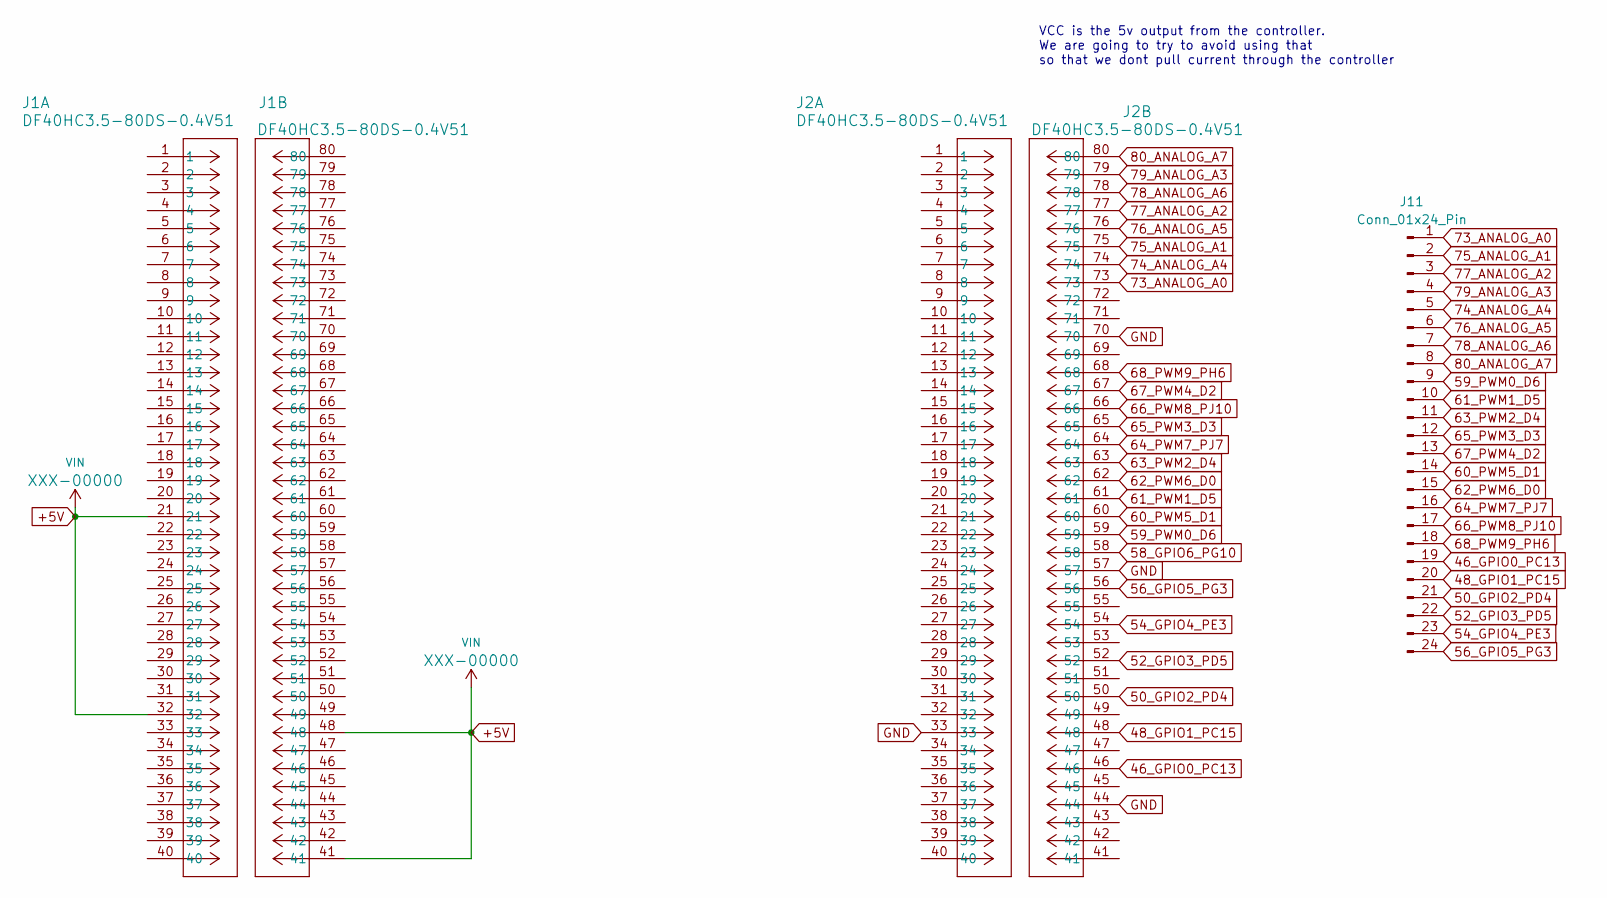
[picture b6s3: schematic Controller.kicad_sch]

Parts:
J1, J2: DF40HC3.5-80DS-0.4V51; DF40HC3580DS04V58
J11: Conn_01x24_Pin; PinHeader_1x24_P2.54mm_Vertical

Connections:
46_GPIO0_PC13: J2.46, J11.19; also elsewhere on the board
48_GPIO1_PC15: J2.48, J11.20; also elsewhere on the board
50_GPIO2_PD4: J2.50, J11.21; also elsewhere on the board
52_GPIO3_PD5: J2.52, J11.22; also elsewhere on the board
54_GPIO4_PE3: J2.54, J11.23; also elsewhere on the board
56_GPIO5_PG3: J2.56, J11.24; also elsewhere on the board
58_GPIO6_PG10: J2.58; also elsewhere on the board
59_PWM0_D6: J2.59, J11.9; also elsewhere on the board
60_PWM5_D1: J2.60, J11.14; also elsewhere on the board
61_PWM1_D5: J2.61, J11.10; also elsewhere on the board
62_PWM6_D0: J2.62, J11.15; also elsewhere on the board
63_PWM2_D4: J2.63, J11.11; also elsewhere on the board
64_PWM7_PJ7: J2.64, J11.16; also elsewhere on the board
65_PWM3_D3: J2.65, J11.12; also elsewhere on the board
66_PWM8_PJ10: J2.66, J11.17; also elsewhere on the board
67_PWM4_D2: J2.67, J11.13; also elsewhere on the board
68_PWM9_PH6: J2.68, J11.18; also elsewhere on the board
73_ANALOG_A0: J2.73, J11.1; also elsewhere on the board
74_ANALOG_A4: J2.74, J11.5; also elsewhere on the board
75_ANALOG_A1: J2.75, J11.2; also elsewhere on the board
76_ANALOG_A5: J2.76, J11.6; also elsewhere on the board
77_ANALOG_A2: J2.77, J11.3; also elsewhere on the board
78_ANALOG_A6: J2.78, J11.7; also elsewhere on the board
79_ANALOG_A3: J2.79, J11.4; also elsewhere on the board
80_ANALOG_A7: J2.80, J11.8; also elsewhere on the board
+5V: J1.21, J1.32, J1.41, J1.48; also elsewhere on the board
GND: J2.33, J2.44, J2.57, J2.70; also elsewhere on the board

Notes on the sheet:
VCC is the 5v output from the controller. We are going to try to avoid using that so that we dont pull current through the controller
